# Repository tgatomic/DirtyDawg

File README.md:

# DirtyDawg

A school project in order to learn and improve our skills in Embedded Systems.

The project consist of a RC car with custom software that detect obstacles and report
the distance to the objects by sending the data over bluetooth to the remotecontroller
where the distances is printed on a small screen. 

This in order to be able to drive the car without actually being able to see it. If there are
time and money budget over, we plan to ad a camera and FPV screen. Maybe even a second RC
car that follows the first one in its heals. 

The car will sense the distance to obbects, using an IR detection unit that will be controlled
by an atmel chip and send the information over the I2C bus over to the main controller that 
will handle the motor controll and communication over Bluetooth. 

The remote controll will have a Bluetooth module that recieves and sends controll data back to
the car. The controll will be able to do this by having an mico with custom software on it. If
the time budget allows, it can be possible to use a phone instead of the controller to controll 
the car.

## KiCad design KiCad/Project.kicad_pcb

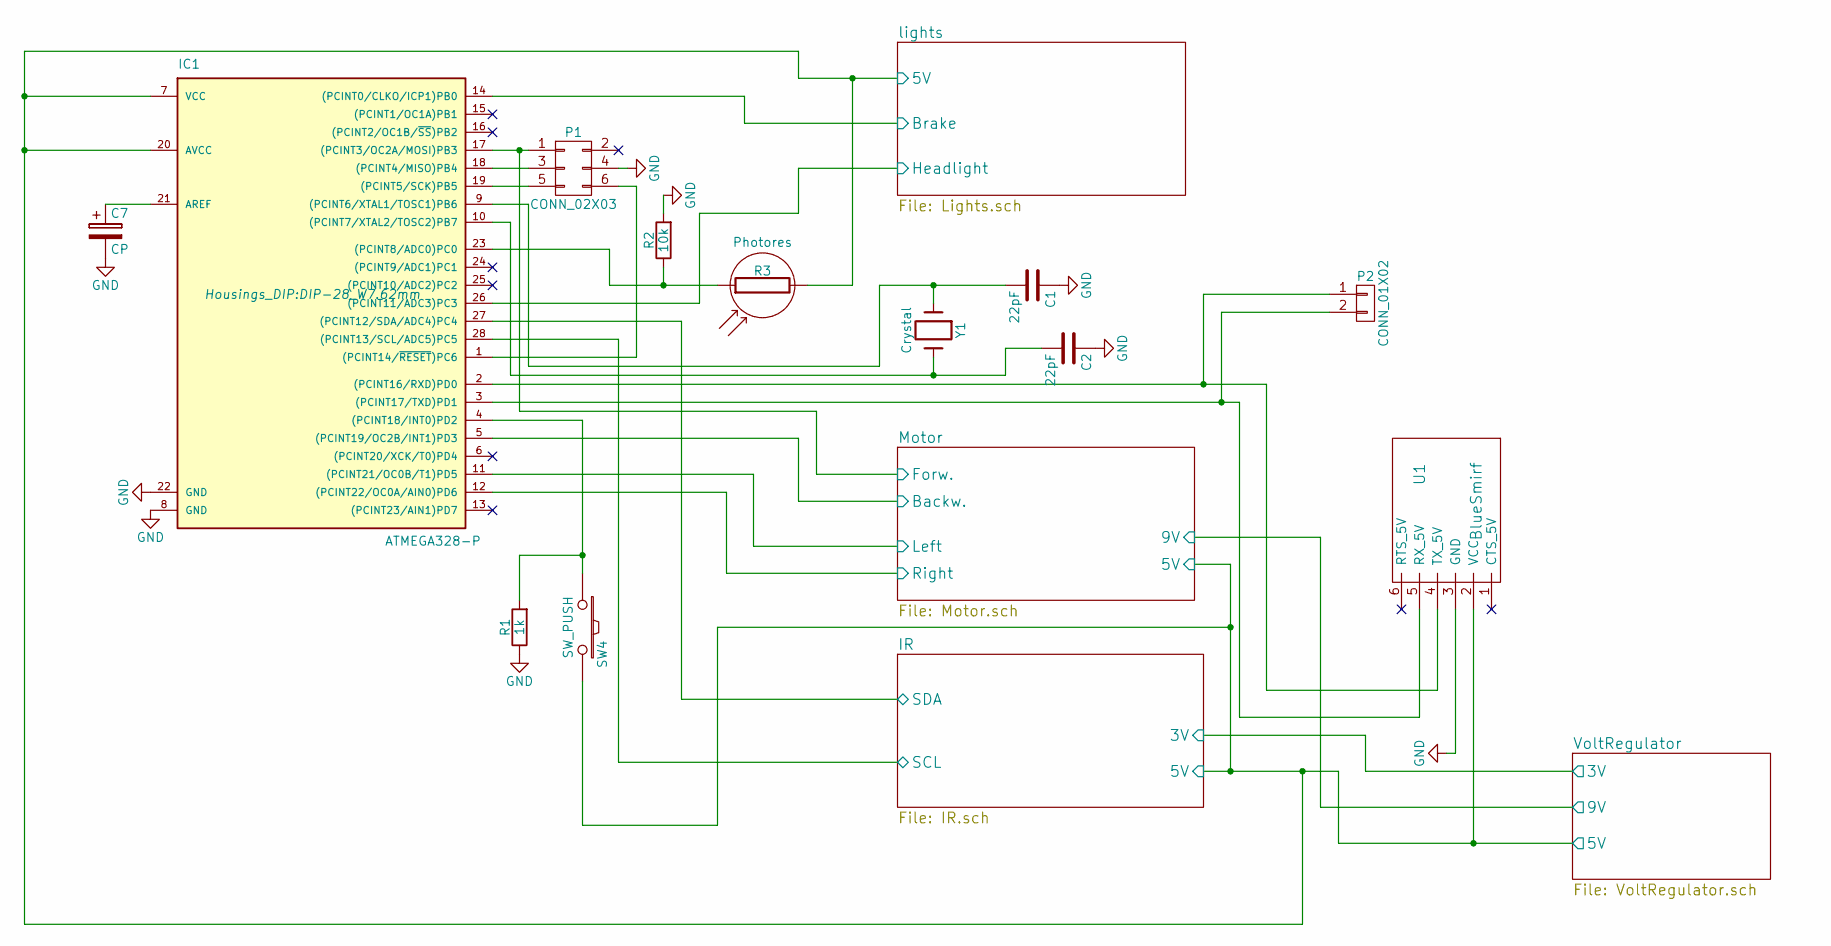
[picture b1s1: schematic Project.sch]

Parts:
C1, C2: 22pF; C_Disc_D3_P2.5
C7: CP; C_Radial_D5_L6_P2.5
IC1: ATMEGA328-P; DIP-28_W7.62mm
P1: CONN_02X03; Pin_Header_Straight_2x03
P2: CONN_01X02; Pin_Header_Straight_1x02
R1: 1k; Resistor_Vertical_RM5mm
R2: 10k; Resistor_Vertical_RM5mm
R3: Photores; SolderWirePad1mmmodified
SW4: SW_PUSH; SolderWirePad1mmmodified
U1: BlueSmirf; Pin_Header_Straight_1x06_Pitch2.00mm
Y1: Crystal; Crystal_HC52-U_Vertical

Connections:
/IR/5V: IC1.7 (VCC), IC1.20 (AVCC), R3.2, SW4.2, U1.2 (VCC); also elsewhere on the board
/IR/SCL: IC1.28 ((PCINT13/SCL/ADC5)PC5); also elsewhere on the board
/IR/SDA: IC1.27 ((PCINT12/SDA/ADC4)PC4); also elsewhere on the board
/Motor/Backw.: IC1.5 ((PCINT19/OC2B/INT1)PD3); also elsewhere on the board
/Motor/Forw.: IC1.17 ((PCINT3/OC2A/MOSI)PB3), P1.1; also elsewhere on the board
/Motor/Left: IC1.11 ((PCINT21/OC0B/T1)PD5); also elsewhere on the board
/Motor/Right: IC1.12 ((PCINT22/OC0A/AIN0)PD6); also elsewhere on the board
/lights/Brake: IC1.14 ((PCINT0/CLKO/ICP1)PB0); also elsewhere on the board
/lights/Headlight: IC1.26 ((PCINT11/ADC3)PC3); also elsewhere on the board
GND: C1.1, C2.1, C7.2, IC1.8 (GND), IC1.22 (GND), P1.4, R1.1, R2.2, U1.3 (GND); also elsewhere on the board
unnamed: C1.2, IC1.9 ((PCINT6/XTAL1/TOSC1)PB6), Y1.1
unnamed: C2.2, IC1.10 ((PCINT7/XTAL2/TOSC2)PB7), Y1.2
unnamed: C7.1, IC1.21 (AREF)
unnamed: IC1.1 ((PCINT14/~RESET~)PC6), P1.6
unnamed: IC1.2 ((PCINT16/RXD)PD0), P2.1, U1.4 (TX_5V)
unnamed: IC1.3 ((PCINT17/TXD)PD1), P2.2, U1.5 (RX_5V)
unnamed: IC1.4 ((PCINT18/INT0)PD2), R1.2, SW4.1
unnamed: IC1.18 ((PCINT4/MISO)PB4), P1.3
unnamed: IC1.19 ((PCINT5/SCK)PB5), P1.5
unnamed: IC1.23 ((PCINT8/ADC0)PC0), R2.1, R3.1

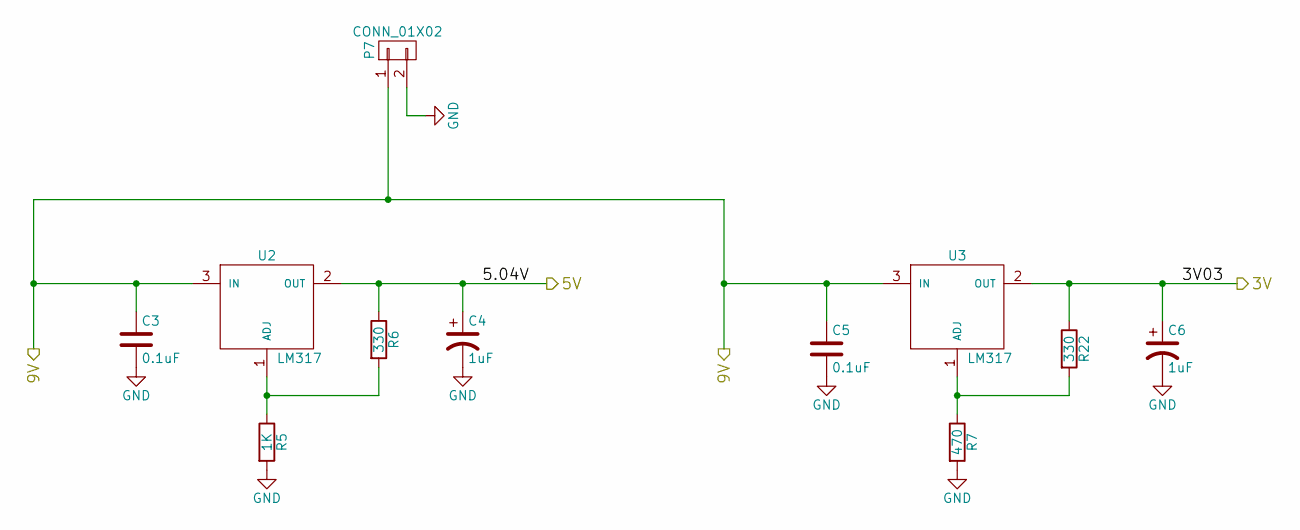
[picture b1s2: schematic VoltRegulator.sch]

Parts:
C3, C5: 0.1uF; C_Disc_D3_P2.5
C4, C6: 1uF; C_Radial_D5_L6_P2.5
P7: CONN_01X02; Pin_Header_Straight_1x02
R5: 1K; Resistor_Vertical_RM5mm
R6, R22: 330; Resistor_Vertical_RM5mm
R7: 470; Resistor_Vertical_RM5mm
U2, U3: LM317; TO-220_Neutral123_Vertical

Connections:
/IR/3V: C6.1, R22.1, U3.2 (OUT); also elsewhere on the board
/IR/5V: C4.1, R6.1, U2.2 (OUT); also elsewhere on the board
/Motor/9V: C3.1, C5.1, P7.1, U2.3 (IN), U3.3 (IN); also elsewhere on the board
GND: C3.2, C4.2, C5.2, C6.2, P7.2, R5.2, R7.2; also elsewhere on the board
unnamed: R5.1, R6.2, U2.1 (ADJ)
unnamed: R7.1, R22.2, U3.1 (ADJ)

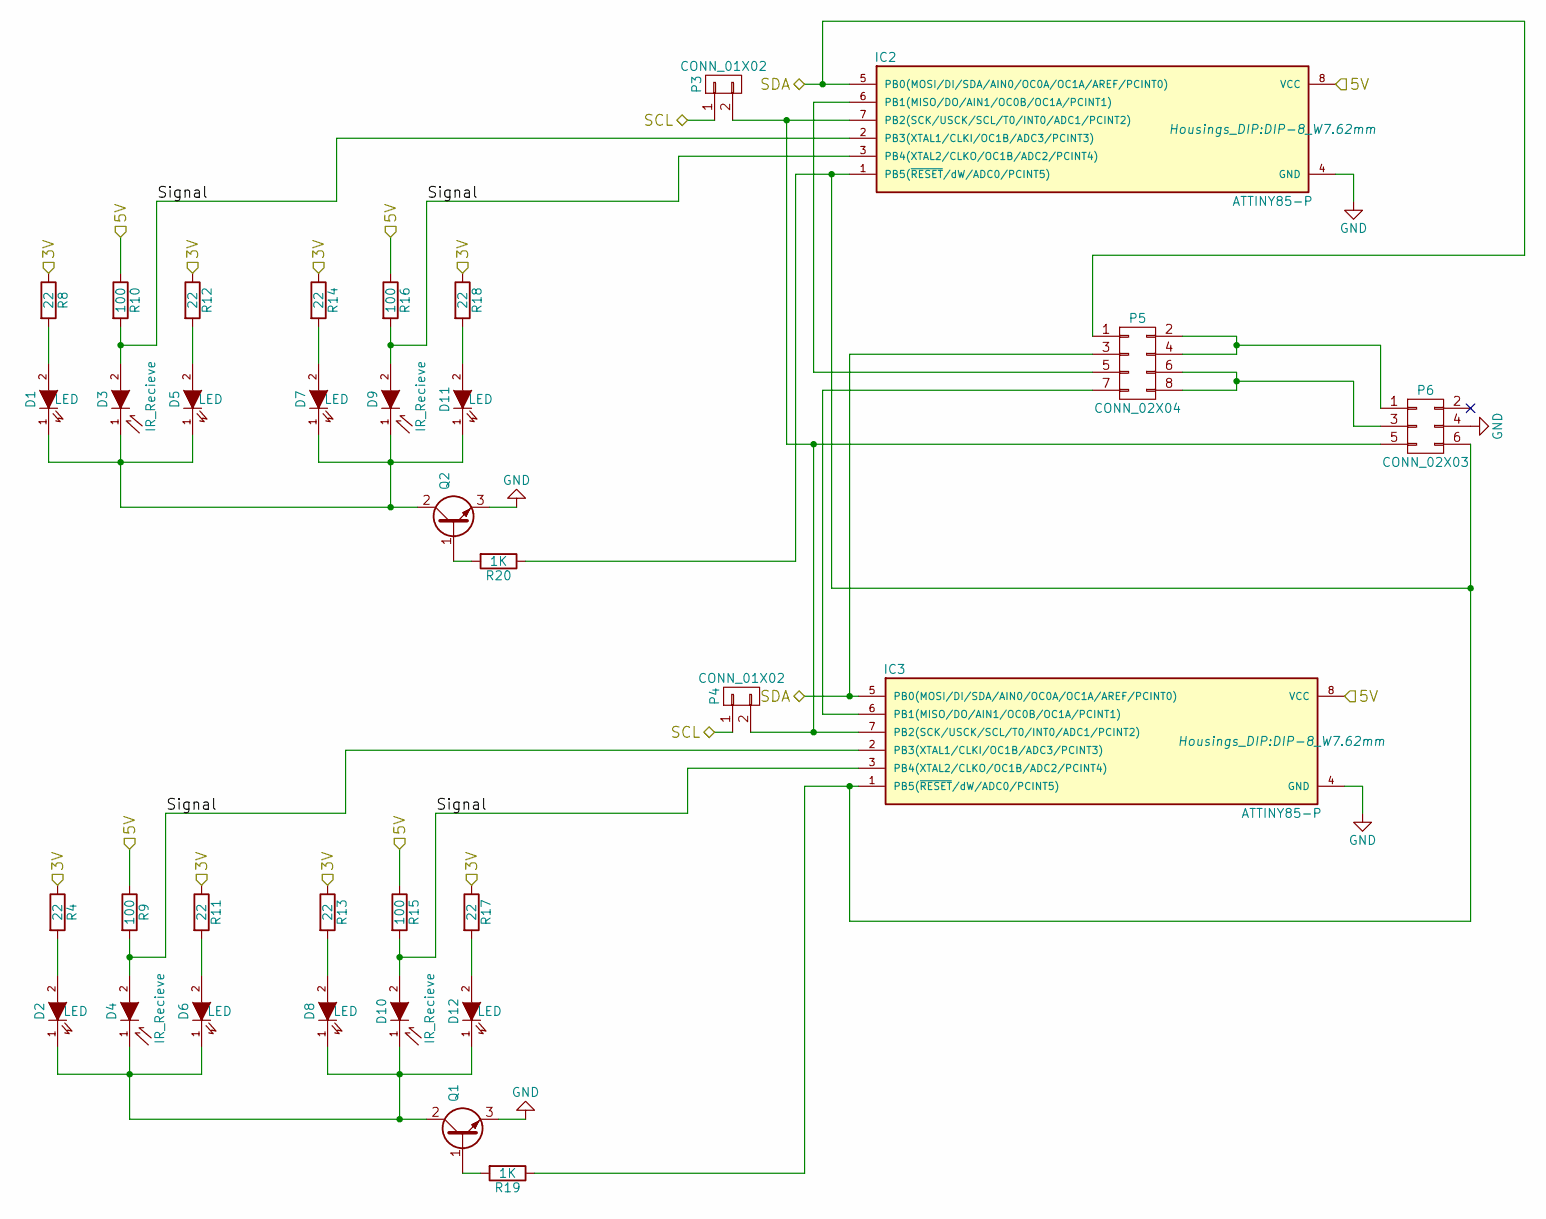
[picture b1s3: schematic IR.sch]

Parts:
D1, D2, D5, D6, D7, D8, D11, D12: LED; SolderWirePad1mmmodified
D3, D4, D9, D10: IR_Recieve; SolderWirePad1mmmodified
IC2, IC3: ATTINY85-P; DIP-8_W7.62mm
P3, P4: CONN_01X02; Pin_Header_Straight_2x01
P5: CONN_02X04; Pin_Header_Straight_2x04
P6: CONN_02X03; Pin_Header_Straight_2x03
Q1, Q2: Q_NPN_BCE; TO-92_Inline_Narrow_Oval
R4, R8, R11, R12, R13, R14, R17, R18: 22; Resistor_Vertical_RM5mm
R9, R10, R15, R16: 100; Resistor_Vertical_RM5mm
R19, R20: 1K; Resistor_Vertical_RM5mm

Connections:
/IR/3V: R4.1, R8.1, R11.1, R12.1, R13.1, R14.1, R17.1, R18.1; also elsewhere on the board
/IR/5V: IC2.8 (VCC), IC3.8 (VCC), R9.1, R10.1, R15.1, R16.1; also elsewhere on the board
/IR/SCL: P3.1, P4.1; also elsewhere on the board
/IR/SDA: IC2.5 (PB0(MOSI/DI/SDA/AIN0/OC0A/OC1A/AREF/PCI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), IC3.5 (PB0(MOSI/DI/SDA/AIN0/OC0A/OC1A/AREF/PCI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), P5.1, P5.3; also elsewhere on the board
/IR/Signal: D3.2 (A), D4.2 (A), D9.2 (A), D10.2 (A), IC2.2 (PB3(XTAL1/CLKI/OC1B/ADC3/PCINT3)), IC2.3 (PB4(XTAL2/CLKO/OC1B/ADC2/PCINT4)), IC3.2 (PB3(XTAL1/CLKI/OC1B/ADC3/PCINT3)), IC3.3 (PB4(XTAL2/CLKO/OC1B/ADC2/PCINT4)), R9.2, R10.2, R15.2, R16.2
GND: IC2.4 (GND), IC3.4 (GND), P6.4, Q1.3 (E), Q2.3 (E); also elsewhere on the board
unnamed: D1.1 (K), D3.1 (K), D5.1 (K), D7.1 (K), D9.1 (K), D11.1 (K), Q2.2 (C)
unnamed: D1.2 (A), R8.2
unnamed: D2.2 (A), R4.2
unnamed: D5.2 (A), R12.2
unnamed: D6.2 (A), R11.2
unnamed: D7.2 (A), R14.2
unnamed: D8.2 (A), R13.2
unnamed: D2.1 (K), D4.1 (K), D6.1 (K), D8.1 (K), D10.1 (K), D12.1 (K), Q1.2 (C)
unnamed: D11.2 (A), R18.2
unnamed: D12.2 (A), R17.2
unnamed: IC2.1 (PB5(~RESET~/dW/ADC0/PCINT5)), IC3.1 (PB5(~RESET~/dW/ADC0/PCINT5)), P6.6, R19.1, R20.1
unnamed: IC2.6 (PB1(MISO/DO/AIN1/OC0B/OC1A/PCINT1)), P5.5
unnamed: IC2.7 (PB2(SCK/USCK/SCL/T0/INT0/ADC1/PCINT2)), IC3.7 (PB2(SCK/USCK/SCL/T0/INT0/ADC1/PCINT2)), P3.2, P4.2, P6.5
unnamed: IC3.6 (PB1(MISO/DO/AIN1/OC0B/OC1A/PCINT1)), P5.7
unnamed: P5.2, P5.4, P6.1
unnamed: P5.6, P5.8, P6.3
unnamed: Q1.1 (B), R19.2
unnamed: Q2.1 (B), R20.2

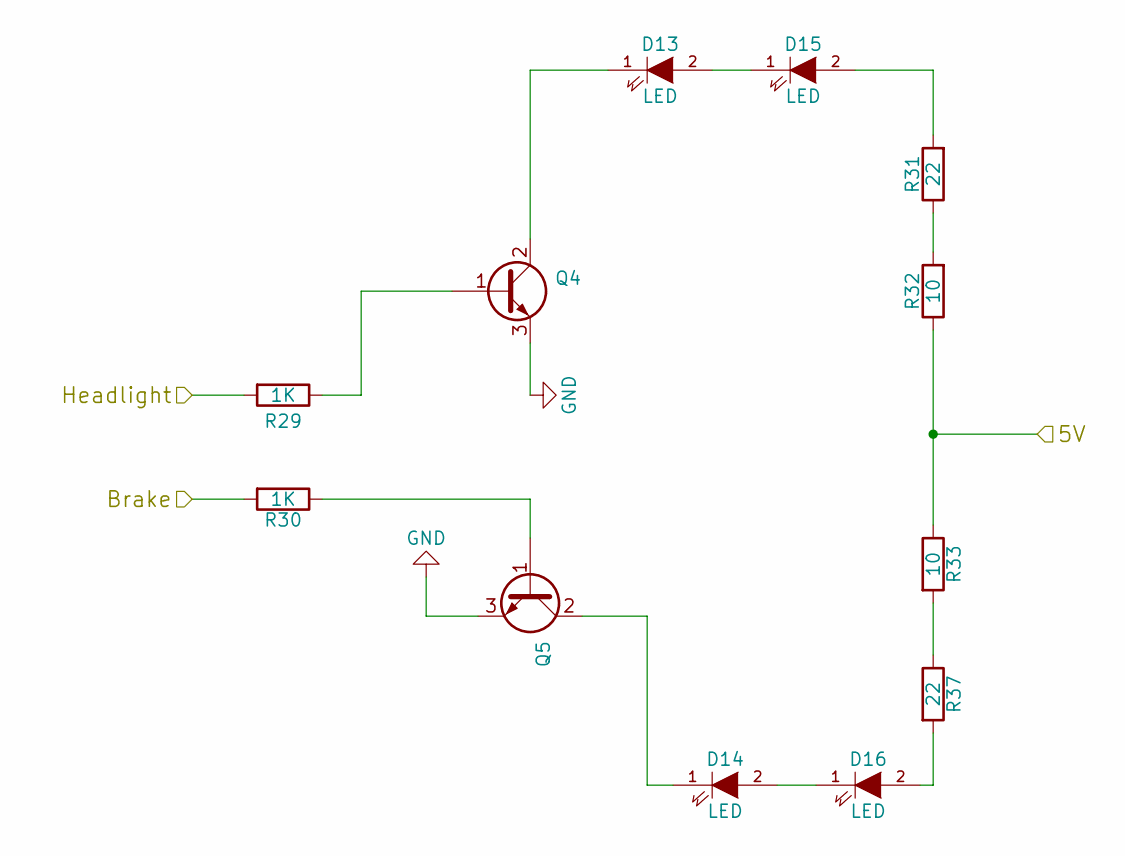
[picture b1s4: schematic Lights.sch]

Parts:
D13, D14, D15, D16: LED; SolderWirePad1mmmodified
Q4: Q_NPN_BCE; TO-92_Inline_Narrow_Oval
Q5: NPN; TO-92_Inline_Narrow_Oval
R29, R30: 1K; Resistor_Vertical_RM5mm
R31, R37: 22; Resistor_Vertical_RM5mm
R32, R33: 10; Resistor_Vertical_RM5mm

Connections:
/IR/5V: R32.1, R33.1; also elsewhere on the board
/lights/Brake: R30.2; also elsewhere on the board
/lights/Headlight: R29.2; also elsewhere on the board
GND: Q4.3 (E), Q5.3 (E); also elsewhere on the board
unnamed: D13.1 (K), Q4.2 (C)
unnamed: D13.2 (A), D15.1 (K)
unnamed: D14.1 (K), Q5.2 (C)
unnamed: D14.2 (A), D16.1 (K)
unnamed: D15.2 (A), R31.2
unnamed: D16.2 (A), R37.2
unnamed: Q4.1 (B), R29.1
unnamed: Q5.1 (B), R30.1
unnamed: R31.1, R32.2
unnamed: R33.2, R37.1

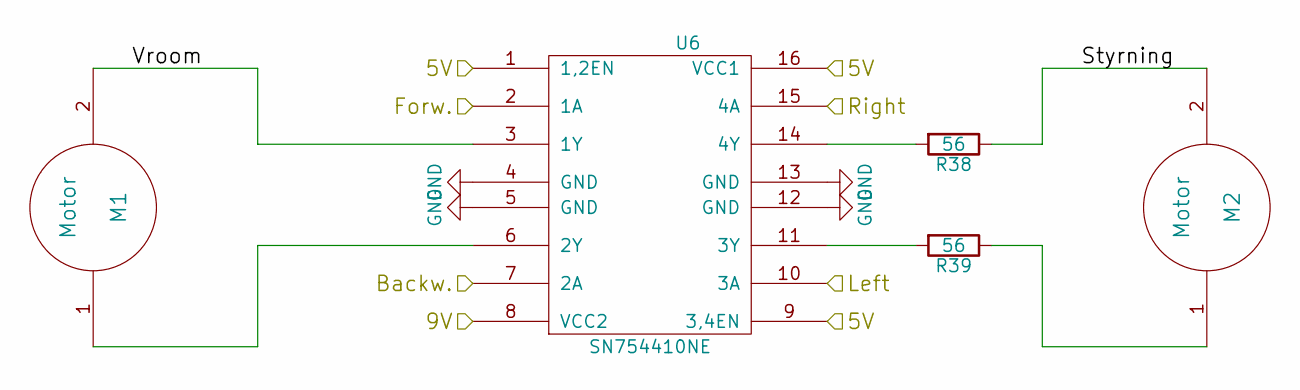
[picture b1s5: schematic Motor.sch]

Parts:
M1, M2: Motor; SolderWirePad1mmmodified
R38, R39: 56; Resistor_Vertical_RM5mm
U6: SN754410NE; DIP-16_W7.62mm_LongPads

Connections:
/IR/5V: U6.1 (1,2EN), U6.9 (3,4EN), U6.16 (VCC1); also elsewhere on the board
/Motor/9V: U6.8 (VCC2); also elsewhere on the board
/Motor/Backw.: U6.7 (2A); also elsewhere on the board
/Motor/Forw.: U6.2 (1A); also elsewhere on the board
/Motor/Left: U6.10 (3A); also elsewhere on the board
/Motor/Right: U6.15 (4A); also elsewhere on the board
/Motor/Styrning: M2.2, R38.1
/Motor/Vroom: M1.2, U6.3 (1Y)
GND: U6.4 (GND), U6.5 (GND), U6.12 (GND), U6.13 (GND); also elsewhere on the board
unnamed: M1.1, U6.6 (2Y)
unnamed: M2.1, R39.1
unnamed: R38.2, U6.14 (4Y)
unnamed: R39.2, U6.11 (3Y)

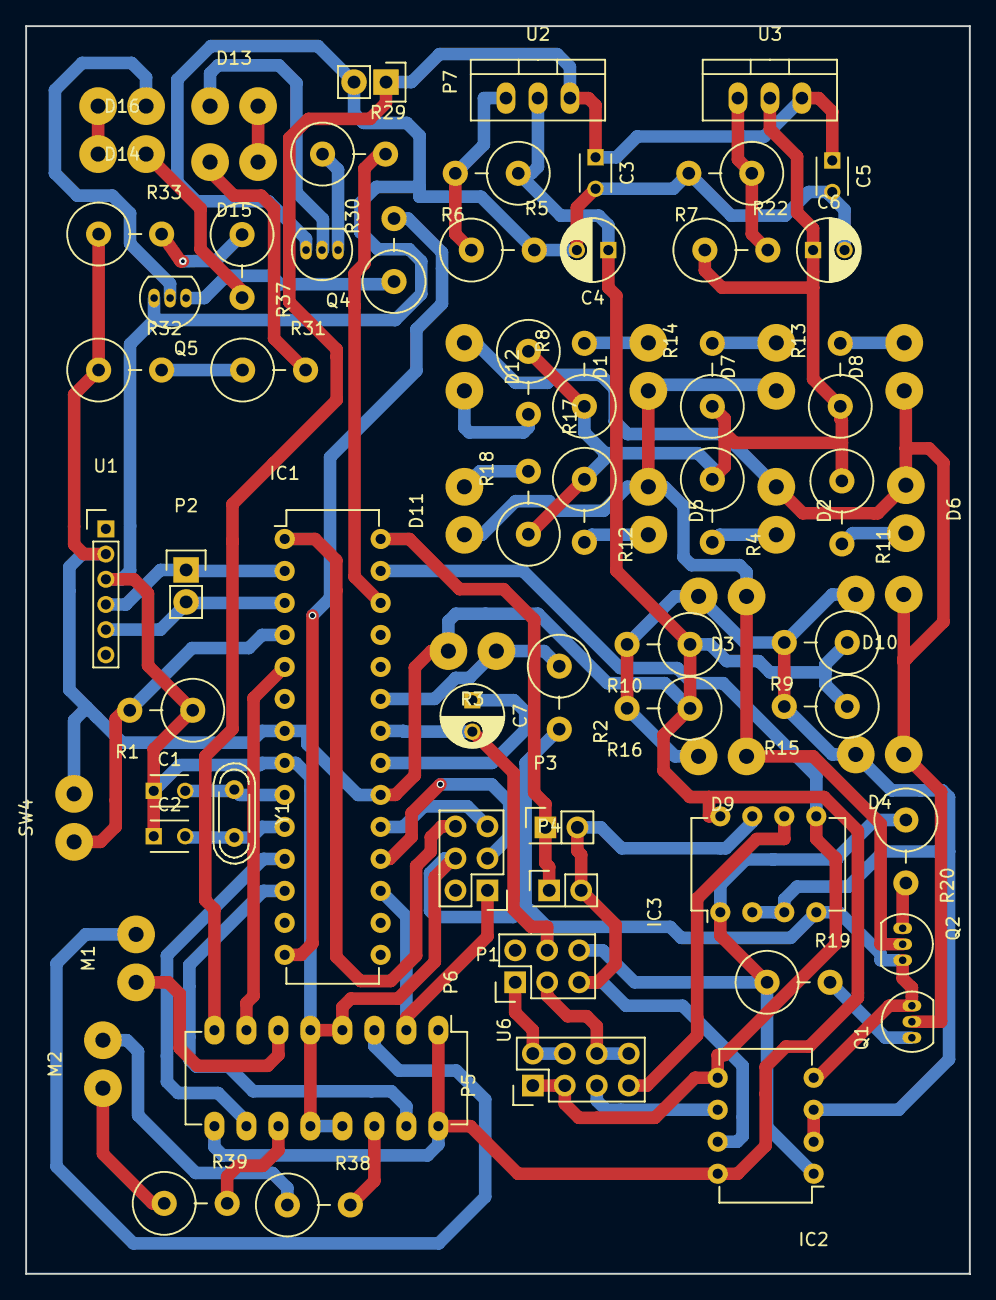
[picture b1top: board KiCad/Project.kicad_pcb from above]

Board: 2 copper layers, 74.9 x 99.1 mm, 74 parts (0 on the bottom side), 59 nets.

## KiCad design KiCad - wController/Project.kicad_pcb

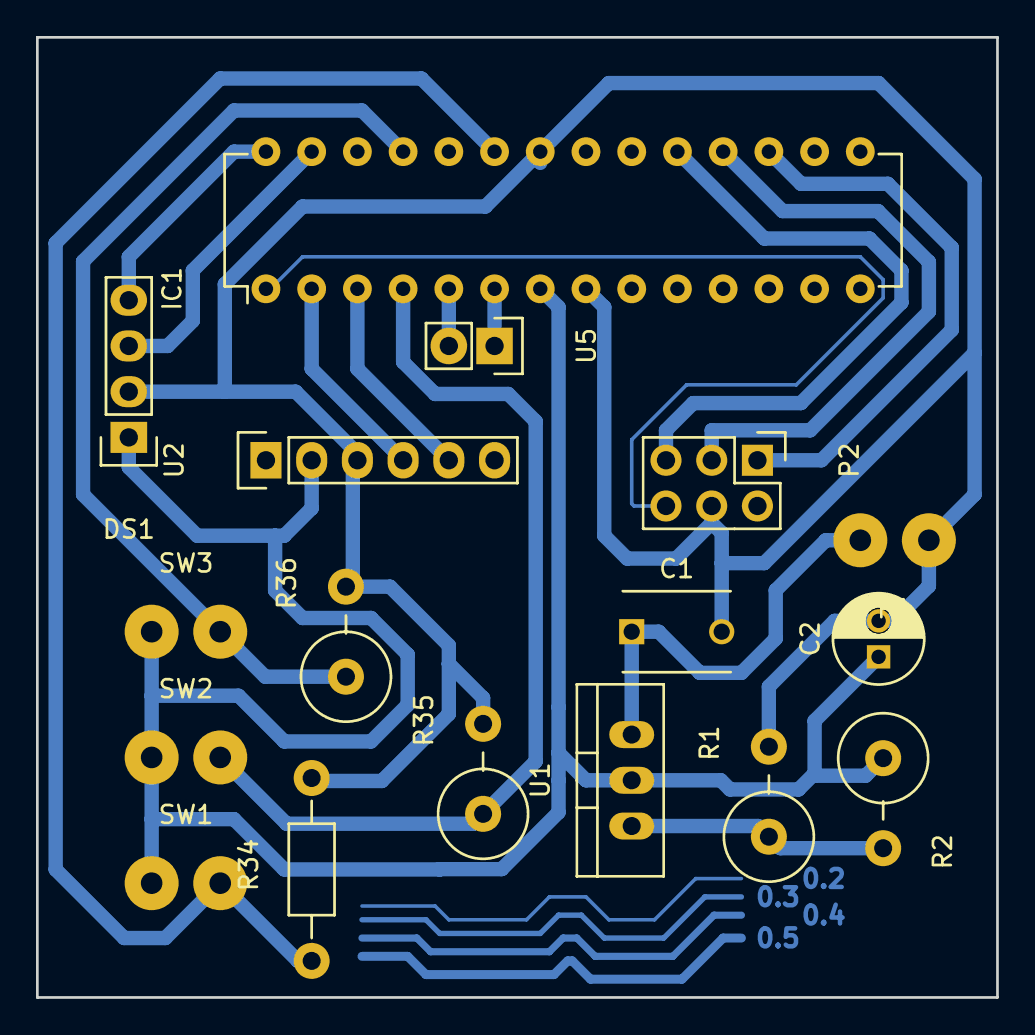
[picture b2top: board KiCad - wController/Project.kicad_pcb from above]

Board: 2 copper layers, 53.3 x 53.3 mm, 17 parts (0 on the bottom side), 17 nets.

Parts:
C1: 0.1uF; C_Disc_D6_P5
C2: 1uF; C_Radial_D5_L11_P2
DS1: I2C_LCD16X2; Pin_Header_Straight_1x04
IC1: ATMEGA168-P; DIP-28_W7.62mm
P1: 9V; SolderWirePad1mmmodified
P2: SPI; Pin_Header_Straight_2x03
R1, R35, R36: 1k; Resistor_Vertical_RM5mm
R2: 330; Resistor_Vertical_RM5mm
R34: 1k; Resistor_Horizontal_RM10mm
SW1: Reverse; SolderWirePad1mmmodified
SW2: Pairing; SolderWirePad1mmmodified
SW3: Lights; SolderWirePad1mmmodified
U1: LM317_SOT223; TO-220_Neutral123_Vertical
U2: BlueSmirf; Pin_Header_Straight_1x06
U5: Linkura; Pin_Header_Straight_1x02

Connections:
/Controller/5V04: C2.1, DS1.1, IC1.7, R2.1, SW1.1, SW2.1, SW3.1, U1.2, U2.2
GND: C1.2, C2.2, DS1.2, IC1.8, IC1.22, P1.1, P2.4, R1.2, R34.2, R35.2, R36.2, U2.3
unnamed: C1.1, P1.2, U1.3
unnamed: DS1.3, IC1.27
unnamed: DS1.4, IC1.28
unnamed: IC1.1, P2.6
unnamed: IC1.2, U2.4
unnamed: IC1.3, U2.5
unnamed: IC1.4, R35.1, SW2.2
unnamed: IC1.5, U5.2
unnamed: IC1.6, U5.1
unnamed: IC1.17, P2.1
unnamed: IC1.18, P2.3
unnamed: IC1.19, P2.5
unnamed: IC1.23, R34.1, SW1.2
unnamed: IC1.25, R36.1, SW3.2
unnamed: R1.1, R2.2, U1.1

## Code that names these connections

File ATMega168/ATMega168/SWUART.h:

#ifdef _AVR_IOM8_H_
#define SRX     PB0     // ICP on Mega8
#define SRXPIN  PINB

#define STX     PB1     // OC1A on Mega8
#define STXDDR  DDRB

#elif _AVR_IOM644_H_

#define SRX		PD2 //INT0 pin
#define SRXPIN	PIND

#define STX		PD3 //INT1 pin
#define STXDDR	DDRD

#elif _AVR_IOM168P_H_

#define SRX		PORTD2
#define SRXPIN	PIND

#define STX		PORTD3
#define STXDDR	DDRD



#else
#error
#error Please add the defines:
#error
#error SRX, SRXPIN, STX, STXDDR
#error
#error for the new target !
#error
#endif

//Typedefs to make life easier
typedef unsigned char  u8;
typedef   signed char  s8;
typedef unsigned short u16;
typedef   signed short s16;
typedef unsigned long  u32;
typedef   signed long  s32;


extern volatile u8 srx_done;

#define kbhit()	(srx_done)	// true if byte received

void suart_init( void );
void sputchar( u8 val );
u8 sgetchar( void );
void sputs( u8 *txt );

struct bits {
	u8 b0:1;
	u8 b1:1;
	u8 b2:1;
	u8 b3:1;
	u8 b4:1;
	u8 b5:1;
	u8 b6:1;
	u8 b7:1;
} __attribute__((__packed__));

#define SBIT_(port,pin) ((*(volatile struct bits*)&port).b##pin)
#define	SBIT(x,y)	SBIT_(x,y)

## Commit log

2016-04-12 Added content to readme
    Wrote a short description
2016-04-12 Added the list of items
2016-04-13 Added documents
    Added Tidsplan, Kravlista, Tidsplan and Kalkyl
2016-04-13 Updated kravlistan
2016-04-18 Lagt upp Testplan och Funktioner
2016-04-18 Added KiCad Project
2016-04-18 Added codeproject for AtmelStudio
2016-04-18 Added functions
2016-04-19 Updated the code
2016-04-19 Added schematicsdocument
    Only the remote controller left
2016-04-25 Added the Hbridge
    The schematics is almost completed with all the values set on resitors
    and all the components should be there. Minor changes is to be expected
    though.
2016-04-25 CHange in motorSchematics
2016-04-25 Added a document with steps.
2016-04-25 Changed values of resistors
2016-04-25 Added code
    Added code to initiate MCU and ports plus started to look at the start
    of bluetooth module.
2016-04-26 Added TWI Header and Source file
2016-04-28 Added PWM TWI ADC to project
    Added initialization functions for PWM, ADC and TWI so it should work
    now.
2016-04-28 Added a state machine
2016-05-01 Added tasklist explenation
2016-05-01 Added anotation and footprints
2016-05-02 Updated code - started with Light state
2016-05-02 Updated Tidsplan
2016-05-02 Added functionality for debugging
2016-05-03 Added functionality for Bluetooth
    Able to go into command mode and connect to another Bluesmirf. Not able
    to detect connection though.
2016-05-04 Started with TWI LCD
2016-05-09 Leftovers
2016-05-09 Uppdaterat tidsplanen
2016-05-10 Compiles a release version
2016-05-10 Second version of TWI to Display
2016-05-10 Updated TWI
2016-05-11 TWI LCD working
    Created a library for the LCD with TWI backpack that works with strings.
2016-05-11 Fixed PWM init
2016-05-11 Updated the schematics and started with the PCB
2016-05-11 Added two files to comit
2016-05-12 Started with the PCB
2016-05-13 Handcontroller LCD
    Added code for the LCD on handcontroller (TWI and interrupt handling)
2016-05-13 Started to do the routing
2016-05-13 Created a new header
    Created a new header called Bluetooth and added its sourcefile and moved
    functions from functions.h that matched better with the BLuettoth header
    and source. Also added a state for pairing in the statemachine.
2016-05-15 Started to finalize all but sensor state
2016-05-15 Autofile
2016-05-16 Added smaller footprints
2016-05-16 Tested the motorcontroller - working
2016-05-16 saved savestate
2016-05-17 Betarelease
    All states are written, interrupt UART is working, all communication is
    working, ADC is working, TWI is working, TWI LCD is working, PWM is
    working. All should be go for testing.
2016-05-17 Release fixes
    Turned on release instead of debug and did some small
    changes/corrections
2016-05-18 Deleted kicad folder before merge with master
2016-05-18 test
2016-05-18 Revert "Added smaller footprints"
    This reverts commit 0613a684753a289cb87120d105616d3a60c555f9.
2016-05-18 Revert "Revert "Added smaller footprints""
    This reverts commit e704f44f413b623022dd61e84b83712d6d051894.
2016-05-18 Fixed files after bad merge
    Everything should be working now..
2016-05-18 Added the backedup data to master
2016-05-18 Updated the pcb to smaller size and footprints
2016-05-19 ATMega 168
    Work in progress
2016-05-19 Added code and created PCB for controller
2016-05-19 Started to try out a software defined UART
2016-05-20 Finalized the software defined UART
2016-05-20 Started with the statemachine
2016-05-23 Small updates
2016-05-23 Changed size of PCB and started with BT communication
2016-05-23 random
2016-05-24 Started with BT communication
2016-05-24 Added wait function for pairing
2016-05-25 BlueSmirf connection working
2016-05-26 Updated controller PCB and added pariing mode to BT
2016-05-27 Updated code for BT pairing and modified vias in PCB
2016-05-27 Car <-> handcontroller communication
    Work in progress.....
2016-05-30 Working
2016-05-31 Still working
2016-06-02 Created a TWI bus for ATTiny
2016-06-02 Added project for ATTiny85 with support for TWI.
    Also made a function where 328p asks for data in txsendbuffer from
    ATtiny, and prints it on the LCD screen.
2016-06-03 Working going on
2016-06-08 Working on
2016-06-08 Working ADC!
2016-06-08 Working
    Communication fixed
    Two buttons fixed
2016-06-13 Working bluetooth command
